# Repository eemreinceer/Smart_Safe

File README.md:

# SmartSafe

ESP32-CAM based RFID access-control and IoT safe prototype.

SmartSafe combines embedded firmware, a physical RFID authorization path, a solenoid-lock driver, event capture, Firebase Realtime Database synchronization, a web dashboard, KiCad PCB sources and Fusion 360 mechanical files.

## What this project demonstrates

- C++ firmware on ESP32-CAM with FreeRTOS tasks and a non-blocking state-machine design.
- Local RFID allowlist authorization using an RC522 reader.
- Fail-closed handling for missing credentials, missing TLS CA data and unprovisioned OTA authentication.
- Solenoid/MOSFET lock-control path with explicit actuator-command state.
- Firebase RTDB event synchronization with an offline queue.
- Append-only event logging and role-separated database rules for device/admin/operator access.
- PlatformIO build and mock-test workflow with GitHub Actions checks.
- KiCad schematic/PCB sources and Fusion 360 enclosure/mechanical sources.

## Architecture

~~~text
RFID allowlist
      |
      v
ESP32-CAM firmware ---> MOSFET / solenoid lock
      |                         |
      |                         +--> commanded lock state
      v
Firebase RTDB <--------- device status and audit events
      ^
      |
Authorized dashboard ---> alarm command request
~~~

The physical RFID decision is local to the device. The cloud and web dashboard do not directly unlock the safe.

## Repository map

- FIRMWARE/Platform.IO/ - ESP32-CAM firmware, mocks and PlatformIO configuration
- FIRMWARE/WEB/akilli-kasa-dashboard/ - dashboard, Firebase config template and RTDB rules
- PCB/ - KiCad schematic and PCB sources
- 3D/ - Fusion 360 source files
- docs/ - physical bring-up and acceptance checklist
- SECURITY.md - security assumptions and reporting guidance

## Local configuration

Secrets are intentionally excluded from Git. Copy the templates locally:

~~~bash
cd FIRMWARE/Platform.IO
cp include/secrets.example.h include/secrets.h

cd ../WEB/akilli-kasa-dashboard/web
cp firebase-config.example.js firebase-config.js
~~~

Do not commit Wi-Fi credentials, Firebase service-account keys, device passwords, OTA secrets, tokens or personal event images. Use separate Firebase identities for the device and dashboard, and deploy the RTDB rules before connecting a real device.

## Build and test

~~~bash
cd FIRMWARE/Platform.IO
pio run -e esp32cam
pio run -e esp32cam-hardware
pio run -e esp32cam-production
./wokwi_test.sh
~~~

The Wokwi/mock path checks firmware behavior and RFID flows; it is not proof of physical lock safety, cloud availability or hardware electrical correctness. Follow the physical bring-up checklist before energizing a real actuator.

## Security boundaries

- RC522 UID matching is not cryptographic authentication and cards can be cloned.
- is_locked represents the commanded actuator state because the prototype has no physical lock-position sensor.
- A solenoid must use an appropriate external supply, common ground and flyback protection.
- ESP32-CAM and RC522 logic are 3.3 V; signal levels and MOSFET gate drive must be verified against the relevant datasheets.
- This is a prototype and must not be treated as the sole security layer for valuable assets.

## Project scope

This is a personal engineering and learning project. It includes AI-assisted development in parts; the repository documents the implemented architecture, security decisions, test paths and limitations rather than claiming production readiness.

## License

No LICENSE file has been added yet. Reuse and redistribution should not be assumed until a license is explicitly added.

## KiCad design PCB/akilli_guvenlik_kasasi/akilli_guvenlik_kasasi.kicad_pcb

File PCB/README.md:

# PCB kaynakları

`akilli_guvenlik_kasasi/` altındaki KiCad proje, şema ve PCB dosyaları tasarım
kaynağıdır.

Repository'deki eski Gerber, drill, zip ve schematic PDF dosyaları güncel RFID +
MOSFET mimarisini temsil etmedikleri için kaldırılmıştır. PCB tasarımı
tamamlanıp ERC/DRC kontrolleri geçmeden bu repository'den üretim dosyası
gönderilmemelidir.

Yeni üretim paketi oluşturulurken en az şu dosyalar aynı KiCad revizyonundan
yeniden üretilmelidir:

- Copper, solder mask ve silkscreen Gerber katmanları
- Edge cuts
- PTH ve NPTH drill dosyaları
- Gerber job dosyası
- Assembly/BOM dokümanları
- Görsel kontrol için schematic PDF

KiCad'in kullanıcıya ve yerel pencere durumuna özel `*.kicad_prl` dosyaları
takip edilmez.

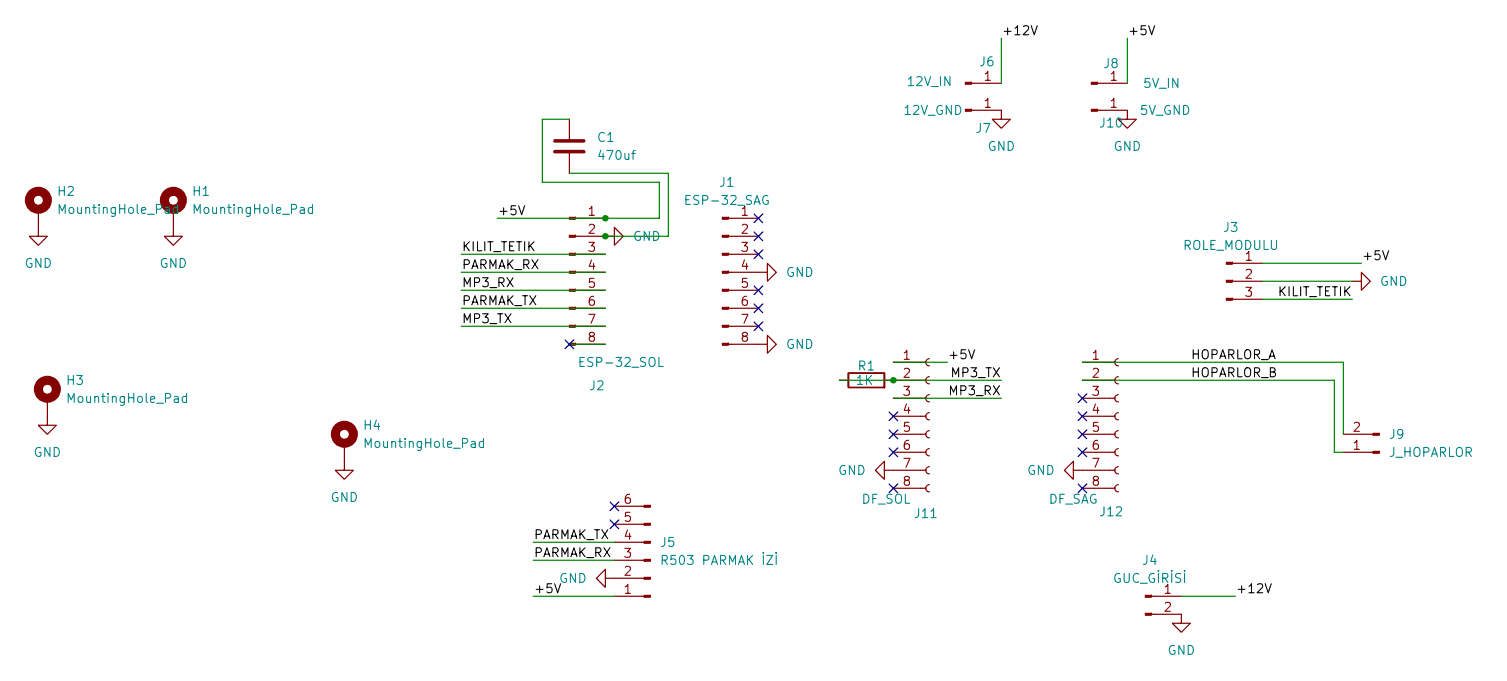
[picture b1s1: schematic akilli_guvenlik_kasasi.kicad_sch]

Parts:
C1: 470uf; CP_Radial_D8.0mm_P3.50mm
H1, H2, H3, H4: MountingHole_Pad; MountingHole_3.2mm_M3_Pad
J1: ESP-32_SAG; PinSocket_1x08_P2.54mm_Vertical
J2: ESP-32_SOL; PinSocket_1x08_P2.54mm_Vertical
J3: ROLE_MODULU; PinSocket_1x03_P2.54mm_Horizontal
J4: GUC_GİRİSİ; TerminalBlock_Phoenix_MKDS-1,5-2-5.08_1x02_P5.08mm_Horizont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
J5: R503 PARMAK İZİ; JST_XH_B6B-XH-A_1x06_P2.50mm_Vertical
J6: 12V_IN; PinSocket_1x01_P2.54mm_Vertical
J7: 12V_GND; PinSocket_1x01_P2.54mm_Vertical
J8: 5V_IN; PinSocket_1x01_P2.54mm_Vertical
J9: J_HOPARLOR; TerminalBlock_Phoenix_MKDS-1,5-2-5.08_1x02_P5.08mm_Horizont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
J10: 5V_GND; PinSocket_1x01_P2.54mm_Vertical
J11: DF_SOL; PinSocket_1x08_P2.54mm_Vertical
J12: DF_SAG; PinSocket_1x08_P2.54mm_Vertical
R1: 1K; R_Axial_DIN0207_L6.3mm_D2.5mm_P7.62mm_Horizontal

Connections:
/+5V: C1.1, J2.1, J3.1, J5.1, J8.1, J11.1
/+12V: J4.1, J6.1
/HOPARLOR_A: J9.2, J12.1
/HOPARLOR_B: J9.1, J12.2
/KILIT_TETIK: J2.3, J3.3
/MP3_RX: J2.5, J11.3
/MP3_TX: J2.7, J11.2, R1.1, R1.2
/PARMAK_RX: J2.4, J5.3
/PARMAK_TX: J2.6, J5.4
GND: C1.2, H1.1, H2.1, H3.1, H4.1, J1.4, J1.8, J2.2, J3.2, J4.2, J5.2, J7.1, J10.1, J11.7, J12.7

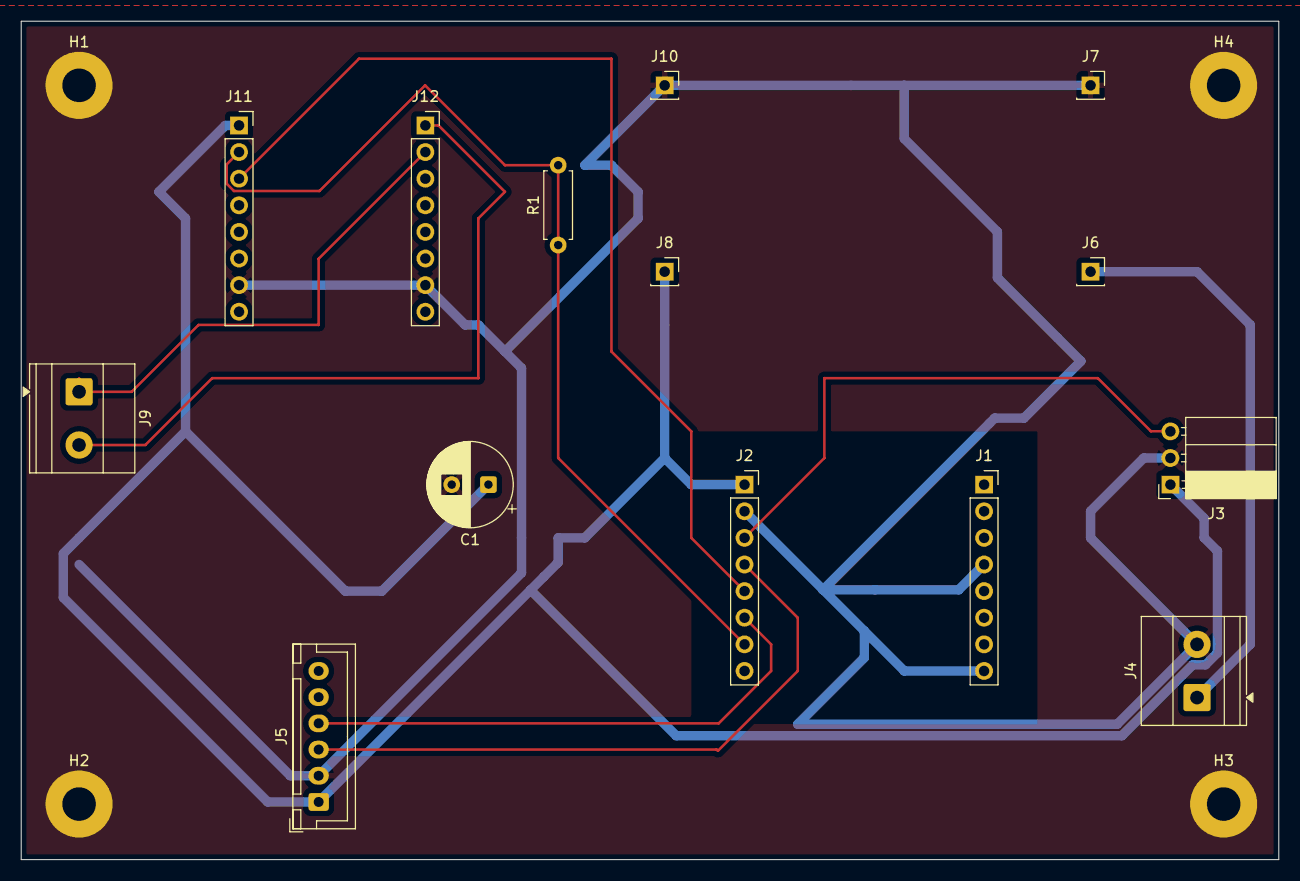
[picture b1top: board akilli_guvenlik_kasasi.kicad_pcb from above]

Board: 2 copper layers, 120.0 x 80.0 mm, 18 parts (0 on the bottom side), 10 nets.

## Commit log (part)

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2026-04-17 SmartSafe
    AI-Powered Smart Safe System with Real-Time Face Recognition and Web Dashboard.
2026-04-17 Update ReadME.md
    Updated project overview, key features, technology stack, project structure, system architecture, and skills gained sections in the ReadME file.
2026-04-19 Update ReadME with project structure and architecture
    Added project structure and system architecture sections.
2026-04-23 Revise ReadME with comprehensive project overview
    Expanded project details, features, and setup instructions in ReadME.
2026-04-25 Initial commit: Akıllı Güvenlik Kasası (Smart Safe) v1.0.0
    - ESP32-CAM firmware (PlatformIO/Arduino) — RFID, solenoid lock, Firebase, OTA, DFPlayer
    - React web dashboard — Firebase Realtime Database, remote unlock
    - Python AI server — DeepFace/ArcFace yüz tanıma, Firebase Admin SDK
    - KiCad PCB tasarımı + Gerber dosyaları
    - Wokwi simülasyon devresi (diagram.json) + entegrasyon test scripti
    - config.h.example ile güvenli credential yönetimi
2026-04-25 Remove python folder — not part of project scope
2026-04-25 Clean up old/duplicate folder structure
    Remove: src/, PCB/ (uppercase), ReadME.md, root requirements.txt,
    web/script.js, web/style.css — replaced by new organized layout.
    Keep: 3D/ models, firmware/, web/src/, pcb/ (lowercase gerber+kicad).
2026-04-25 Add MIT license with author name to README
2026-04-25 Remove all Python references from README
2026-04-25 Update README: bilingual TR/EN, year 2026, remove personal contact info
2026-04-26 Remove real Firebase credentials from firebase.js, replace with placeholders
    https://claude.ai/code/session_0113NZTK5HLoZ26BebgpyTij
2026-04-26 Remove real Firebase credentials, replace with placeholders
2026-05-18 refactor: proje yapısı yeniden düzenlendi, web dashboard güncellendi, .gitignore eklendi
2026-05-18 chore: cleanup
2026-05-18 Add README with project details for SmartSafe
    Added comprehensive project overview, system architecture, technical specifications, and setup instructions for the SmartSafe IoT security system.
